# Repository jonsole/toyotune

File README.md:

# toyotune

Reverse engineering and ROM tuning for Toyota ECUs built on the Toshiba/Denso
8X (D8X) microcontroller — a proprietary part with an instruction set derived
from the Motorola 68HC11.

The best entry point is
**[Inside the 3S-GTE ECU](roms/3S-GTE/gen3/ecu_overview.md)**, an
architectural tour of the 1993 SW20 MR2 turbo ECU: three processors, adaptive
fuel trim and per-cylinder knock learning in 16 KB of ROM.

## What's here

- **[`roms/`](roms/)** — disassembly, annotation and tuned-ROM production.
  One directory per engine family (1G-GTE, 1G-GZE, 1JZ-GTE, 1UZ-FE, 3S-GE,
  3S-GTE, 3VZ-FE, 4A-GE), each holding one subdirectory per ECU part number.
  - [`roms/3S-GTE/`](roms/3S-GTE/) is the most thoroughly documented family —
    its [README](roms/3S-GTE/README.md) maps every part number to market,
    vehicle and CPU, and [`gen3/`](roms/3S-GTE/gen3/) holds the subsystem
    write-ups.
  - [`roms/docs/`](roms/docs/) documents the D8X MCU itself — instruction
    set, opcode matrix, registers — which every family here shares.
  - [`roms/d8x_assembler/`](roms/d8x_assembler/) is a Python reimplementation
    of the D8X assembler, and what the Makefiles actually build with.
- **[`hw/`](hw/)** — the Toyotune interface board: PCB, CPLD and host-MCU
  firmware for reading and rewriting these ECUs, including live access while
  the engine is running.
- **`sw/`** — IDA Pro installs used to open the `.idb` databases.

## Status

Ongoing and incomplete. The 3S-GTE Gen 3 pair is the furthest along; other
families are largely raw disassembly. Coverage is stated honestly in each
document — see
[session_journal.md](roms/3S-GTE/gen3/session_journal.md) for what is done
and what is pending.

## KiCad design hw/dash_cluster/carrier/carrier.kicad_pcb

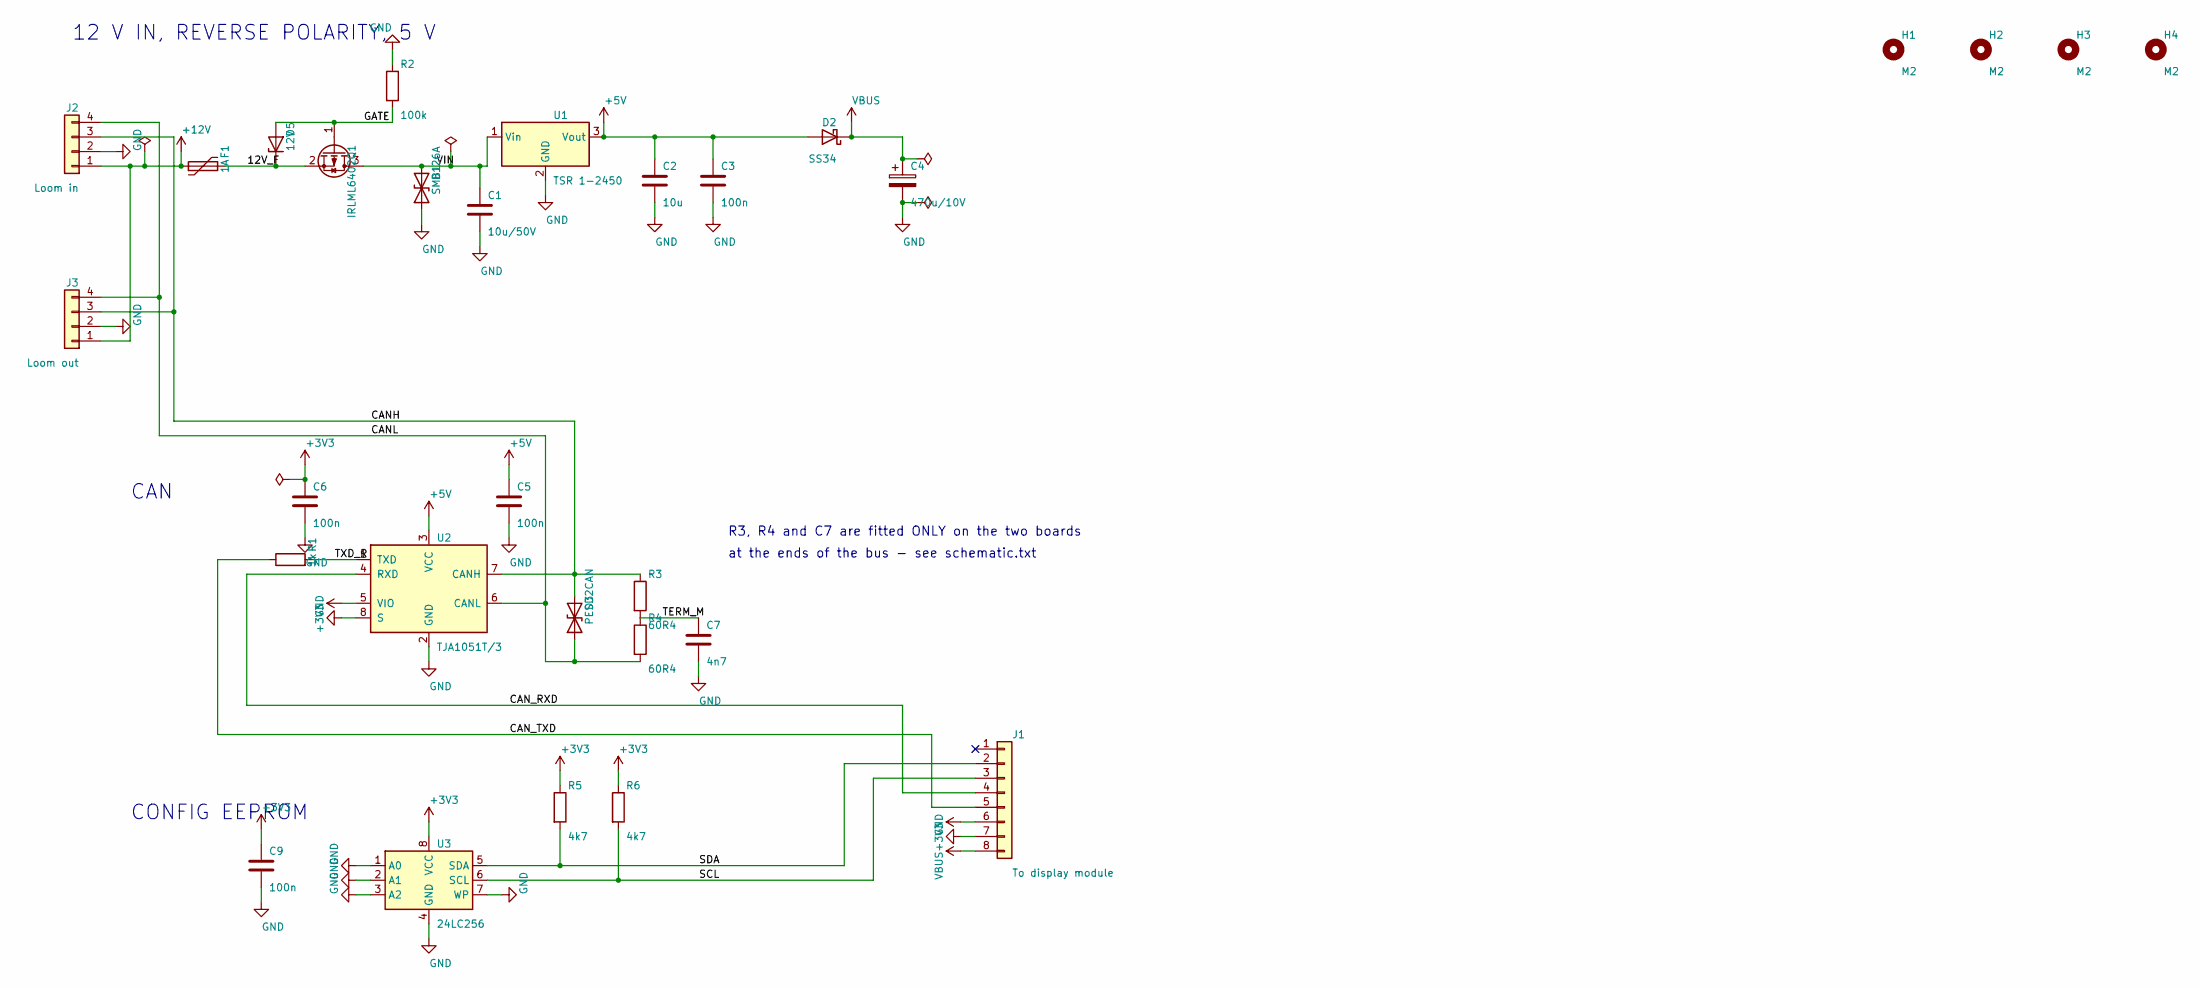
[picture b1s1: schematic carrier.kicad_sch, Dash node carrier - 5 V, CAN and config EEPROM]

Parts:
C1: 10u/50V; C_1206_3216Metric
C2: 10u; C_0805_2012Metric
C3, C5, C6, C9: 100n; C_0603_1608Metric
C4: 470u/10V; CP_Elec_8x10.5
C7: 4n7; C_0603_1608Metric
D1: SMBJ26A; D_SMB
D2: SS34; D_SMA
D3: PESD2CAN; SOT-23
D5: 12V; D_SOD-123
F1: 1A; Fuse_1206_3216Metric
H1, H2, H3, H4: M2; MountingHole_2.2mm_M2
J1: To display module; PinSocket_1x08_P2.54mm_Vertical
J2: Loom in; Molex_Micro-Fit_3.0_43045-0400_2x02_P3.00mm_Horizontal
J3: Loom out; Molex_Micro-Fit_3.0_43045-0400_2x02_P3.00mm_Horizontal
Q1: IRLML6402; SOT-23
R1: 1k; R_0603_1608Metric
R2: 100k; R_0805_2012Metric
R3, R4: 60R4; R_0805_2012Metric
R5, R6: 4k7; R_0603_1608Metric
U1: TSR 1-2450; Converter_DCDC_TRACO_TSR-1_THT
U2: TJA1051T/3; SOIC-8_3.9x4.9mm_P1.27mm
U3: 24LC256; SOIC-8_3.9x4.9mm_P1.27mm

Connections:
+3V3: C6.1, C9.1, J1.6, R5.1, R6.1, U2.5 (VIO), U3.8 (VCC)
+5V: C2.1, C3.1, C5.1, D2.2 (A), U1.3 (Vout), U2.3 (VCC)
+12V: F1.1, J2.1, J3.1
/12V_F: D5.1 (K), F1.2, Q1.2 (S)
/CANH: D3.2 (A2), J2.3, J3.3, R3.1, U2.7 (CANH)
/CANL: D3.1 (A1), J2.4, J3.4, R4.2, U2.6 (CANL)
/CAN_RXD: J1.4, U2.4 (RXD)
/CAN_TXD: J1.5, R1.1
/GATE: D5.2 (A), Q1.1 (G), R2.2
/SCL: J1.3, R6.2, U3.6 (SCL)
/SDA: J1.2, R5.2, U3.5 (SDA)
/TERM_M: C7.1, R3.2, R4.1
/TXD_R: R1.2, U2.1 (TXD)
/VIN: C1.1, D1.2 (A2), Q1.3 (D), U1.1 (Vin)
GND: C1.2, C2.2, C3.2, C4.2, C5.2, C6.2, C7.2, C9.2, D1.1 (A1), J1.7, J2.2, J3.2, R2.1, U1.2 (GND), U2.2 (GND), U2.8 (S), U3.1 (A0), U3.2 (A1), U3.3 (A2), U3.4 (GND), U3.7 (WP)
VBUS: C4.1, D2.1 (K), J1.8

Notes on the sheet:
12 V IN, REVERSE POLARITY, 5 V
CAN
CONFIG EEPROM
R3, R4 and C7 are fitted ONLY on the two boards
at the ends of the bus - see schematic.txt

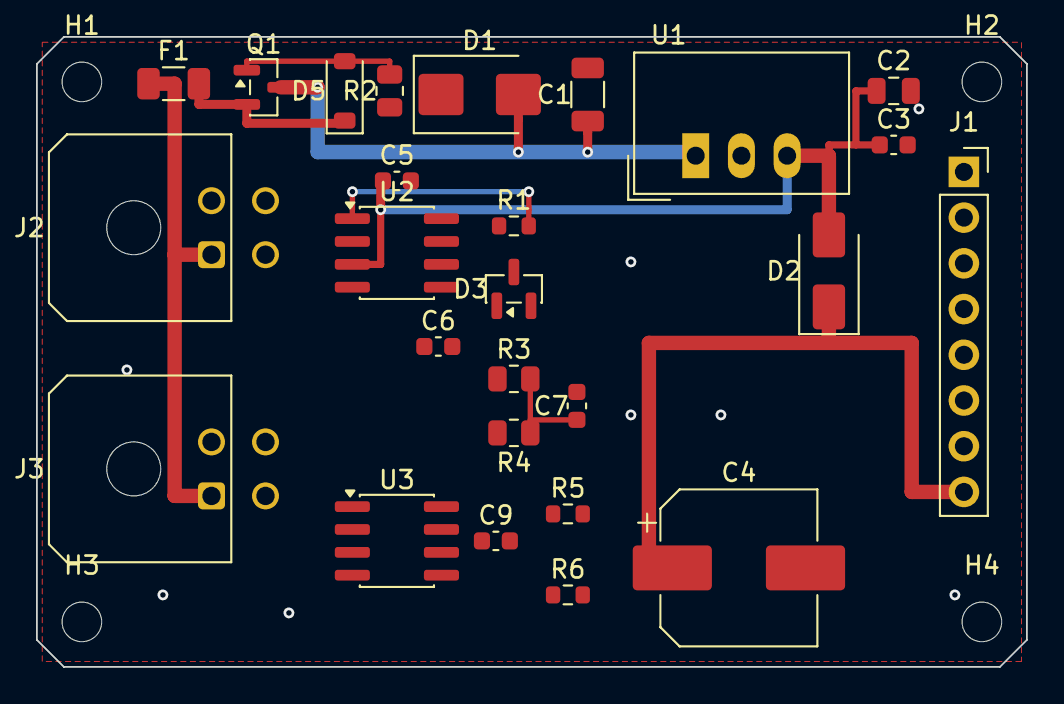
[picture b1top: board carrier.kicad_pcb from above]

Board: 4 copper layers, 55.0 x 35.0 mm, 30 parts (0 on the bottom side), 16 nets.

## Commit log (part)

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2018-05-18 Initial commit with PCB schematics and CPLD VHDL.
2018-05-22 Set theme jekyll-theme-midnight
2018-09-20 Add IDA Free plugin for Denso 8X CPU
2018-09-20 Adding ROMs and tools.
2021-01-05 Set TASMTABS.
2021-01-05 Remove directory
2021-01-05 Add modified ST205 images back in
2026-04-23 Denso 8 docs
2026-04-24 Knock Sensor Details
2026-04-27 Add files via upload
    ADC details
2026-04-27 Add files via upload
    Knock detection details
